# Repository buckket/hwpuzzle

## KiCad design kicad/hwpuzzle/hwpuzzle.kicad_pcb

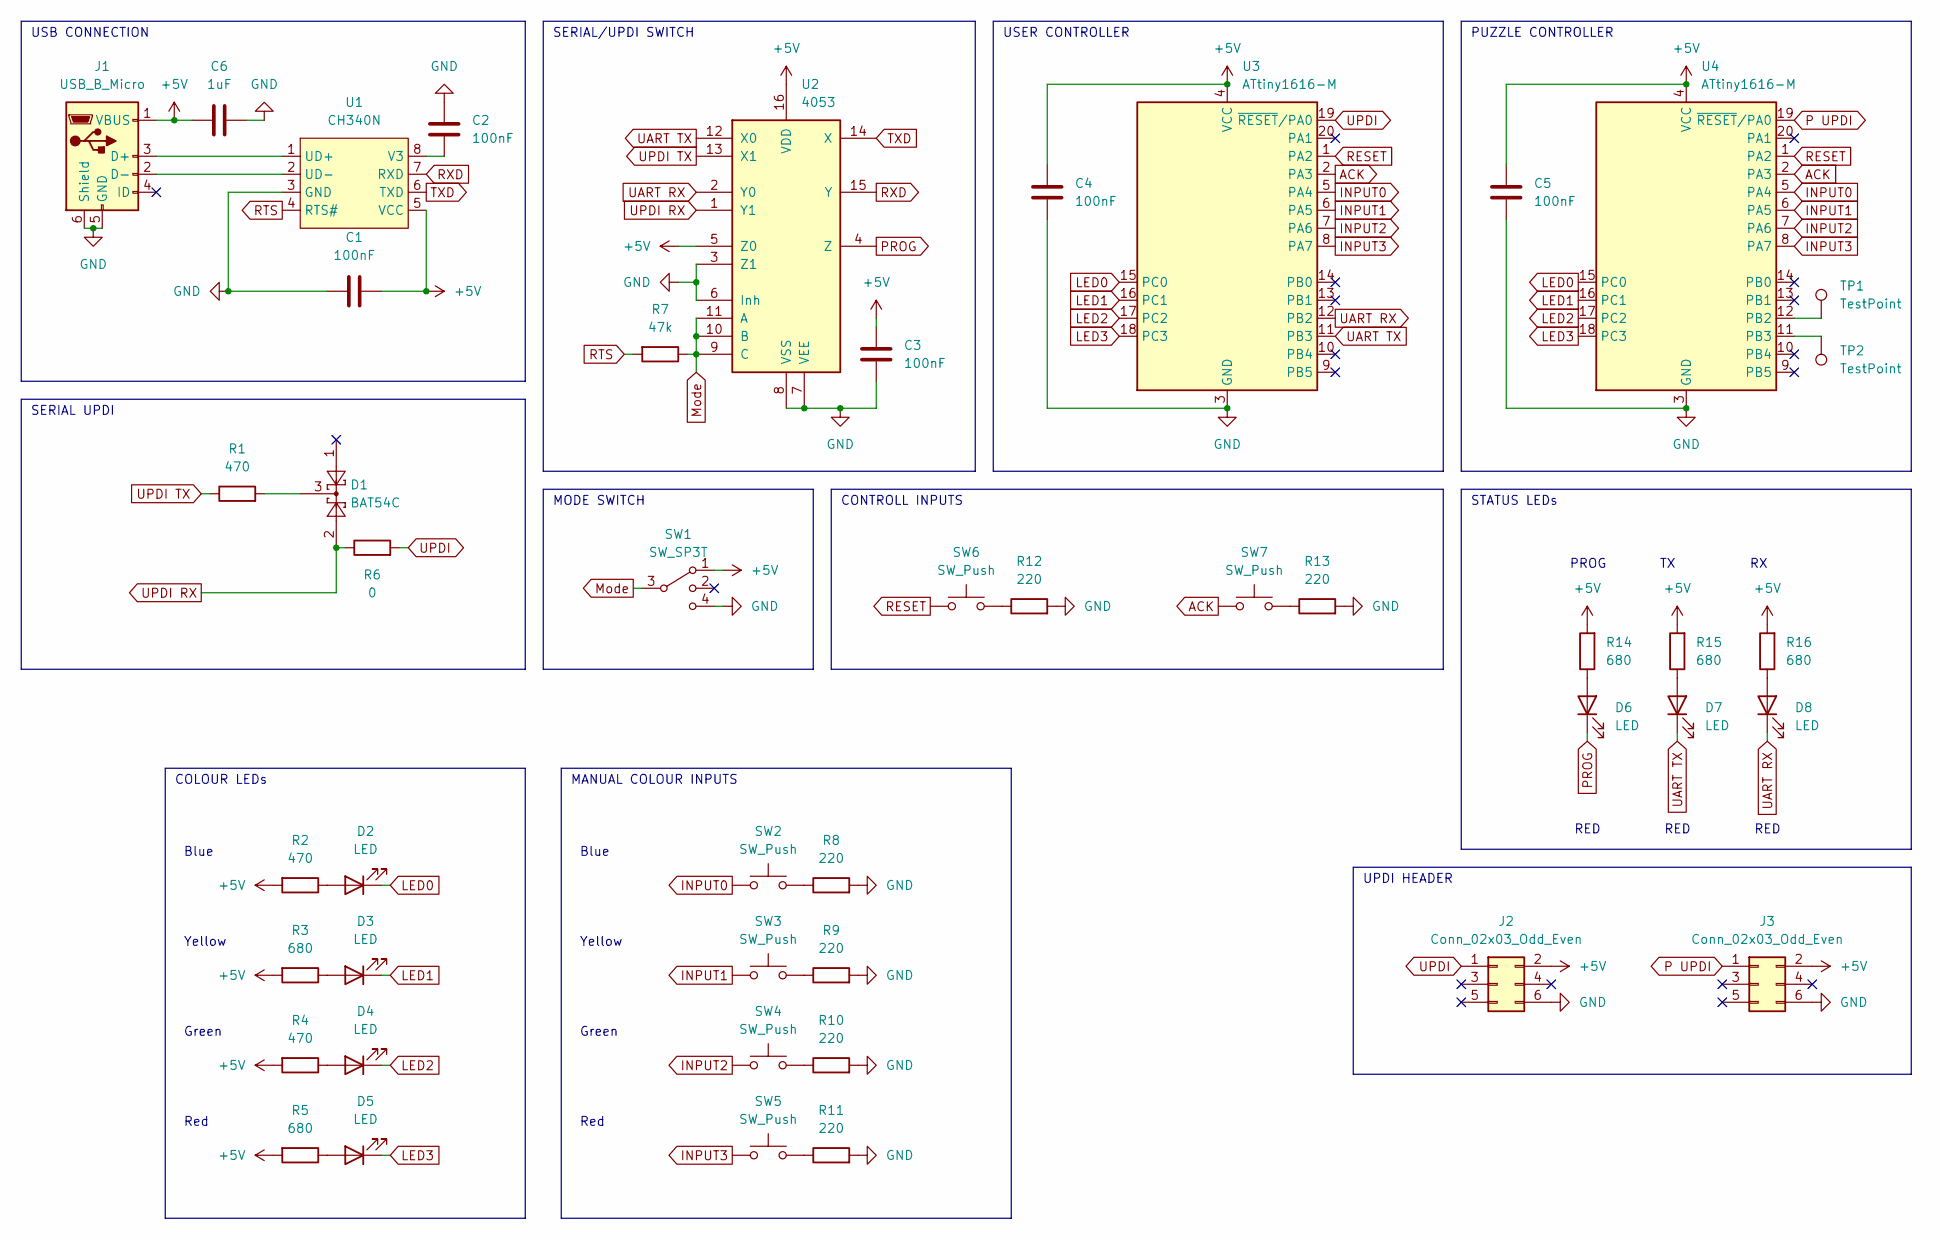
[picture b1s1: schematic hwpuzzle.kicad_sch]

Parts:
C1, C2, C3, C4, C5: 100nF; C_0402_1005Metric; MPN CL05B104KO5NNNC; LCSC C1525
C6: 1uF; C_0402_1005Metric; MPN CL05A105KA5NQNC; LCSC C52923
D1: BAT54C; SOT-23; MPN BAT54C,215; LCSC C37704
D2: LED; LED_0603_1608Metric; MPN 19-217/BHC-ZL1M2RY/3T; LCSC C72041
D3: LED; LED_0603_1608Metric; MPN 19-217/Y5C-AP1Q2/3T; LCSC C74343
D4: LED; LED_0603_1608Metric; MPN 19-217/GHC-YR1S2/3T; LCSC C72043
D5, D6, D7, D8: LED; LED_0603_1608Metric; MPN 19-217/R6C-AL1M2VY/3T; LCSC C72044
J1: USB_B_Micro; MicroXNJ; MPN MicroXNJ; LCSC C404969
J2, J3: Conn_02x03_Odd_Even; PinHeader_2x03_P2.54mm_Vertical; MPN DNP; LCSC DNP
R1, R2, R4: 470; R_0402_1005Metric; MPN 0402WGF4700TCE; LCSC C25117
R3, R5, R14, R15, R16: 680; R_0402_1005Metric; MPN 0402WGF6800TCE; LCSC C25130
R6: 0; R_0402_1005Metric; MPN 0402WGF0000TCE; LCSC C17168
R7: 47k; R_0402_1005Metric; MPN 0402WGF4702TCE; LCSC C25792
R8, R9, R10, R11, R12, R13: 220; R_0402_1005Metric; MPN 0402WGF2200TCE; LCSC C25091
SW1: SW_SP3T; SW_SP3T_PCM13; MPN SSSS812201; LCSC C160878
SW2, SW3, SW4, SW5, SW6, SW7: SW_Push; SW_SPST_TL3342; MPN TS-1187A-B-A-B; LCSC C318884
TP1, TP2: TestPoint; TestPoint_Pad_D1.0mm; MPN DNP; LCSC DNP
U1: CH340N; SOP-8_3.9x4.9mm_P1.27mm; MPN CH340N; LCSC C2977777
U2: 4053; TSSOP-16_4.4x5mm_P0.65mm; MPN CD4053BPWR; LCSC C106760
U3, U4: ATtiny1616-M; VQFN-20-1EP_3x3mm_P0.4mm_EP1.7x1.7mm; MPN ATTINY1616-MNR; LCSC C507118

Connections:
+5V: C1.2, C3.1, C4.1, C5.1, C6.1, J1.1 (VBUS), J2.2, J3.2, R2.2, R3.2, R4.2, R5.2, R14.2, R15.2, R16.2, SW1.1, U1.5 (VCC), U2.5 (Z0), U2.16 (VDD), U3.4 (VCC), U4.4 (VCC)
ACK: SW7.1, U3.2 (PA3), U4.2 (PA3)
GND: C1.1, C2.1, C3.2, C4.2, C5.2, C6.2, J1.5 (GND), J1.6 (Shield), J2.6, J3.6, R8.2, R9.2, R10.2, R11.2, R12.2, R13.2, SW1.4, U1.3 (GND), U2.3 (Z1), U2.6 (Inh), U2.7 (VEE), U2.8 (VSS), U3.3 (GND), U3.21 (GND), U4.3 (GND), U4.21 (GND)
INPUT0: SW2.1, U3.5 (PA4), U4.5 (PA4)
INPUT1: SW3.1, U3.6 (PA5), U4.6 (PA5)
INPUT2: SW4.1, U3.7 (PA6), U4.7 (PA6)
INPUT3: SW5.1, U3.8 (PA7), U4.8 (PA7)
LED0: D2.1 (K), U3.15 (PC0), U4.15 (PC0)
LED1: D3.1 (K), U3.16 (PC1), U4.16 (PC1)
LED2: D4.1 (K), U3.17 (PC2), U4.17 (PC2)
LED3: D5.1 (K), U3.18 (PC3), U4.18 (PC3)
Mode: R7.1, SW1.3, U2.9 (C), U2.10 (B), U2.11 (A)
unnamed: C2.2, U1.8 (V3)
unnamed: D1.3, R1.2
unnamed: D2.2 (A), R2.1
unnamed: D3.2 (A), R3.1
unnamed: D4.2 (A), R4.1
unnamed: D5.2 (A), R5.1
unnamed: D6.2 (A), R14.1
unnamed: D7.2 (A), R15.1
unnamed: D8.2 (A), R16.1
unnamed: J1.2 (D-), U1.2 (UD-)
unnamed: J1.3 (D+), U1.1 (UD+)
unnamed: R8.1, SW2.2
unnamed: R9.1, SW3.2
unnamed: R10.1, SW4.2
unnamed: R11.1, SW5.2
unnamed: R12.1, SW6.2
unnamed: R13.1, SW7.2
unnamed: TP1.1, U4.12 (PB2)
unnamed: TP2.1, U4.11 (PB3)
P UPDI: J3.1, U4.19 (~RESET/PA0)
PROG: D6.1 (K), U2.4 (Z)
RESET: SW6.1, U3.1 (PA2), U4.1 (PA2)
RTS: R7.2, U1.4 (RTS#)
RXD: U1.7 (RXD), U2.15 (Y)
TXD: U1.6 (TXD), U2.14 (X)
UART RX: D8.1 (K), U2.2 (Y0), U3.12 (PB2)
UART TX: D7.1 (K), U2.12 (X0), U3.11 (PB3)
UPDI: J2.1, R6.2, U3.19 (~RESET/PA0)
UPDI RX: D1.2, R6.1, U2.1 (Y1)
UPDI TX: R1.1, U2.13 (X1)

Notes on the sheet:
Blue
MANUAL COLOUR INPUTS
Red
PUZZLE CONTROLLER
Green
Yellow
RED
SERIAL UPDI
UPDI HEADER
PROG
CONTROLL INPUTS
SERIAL/UPDI SWITCH
USB CONNECTION
USER CONTROLLER
MODE SWITCH
STATUS LEDs
COLOUR LEDs

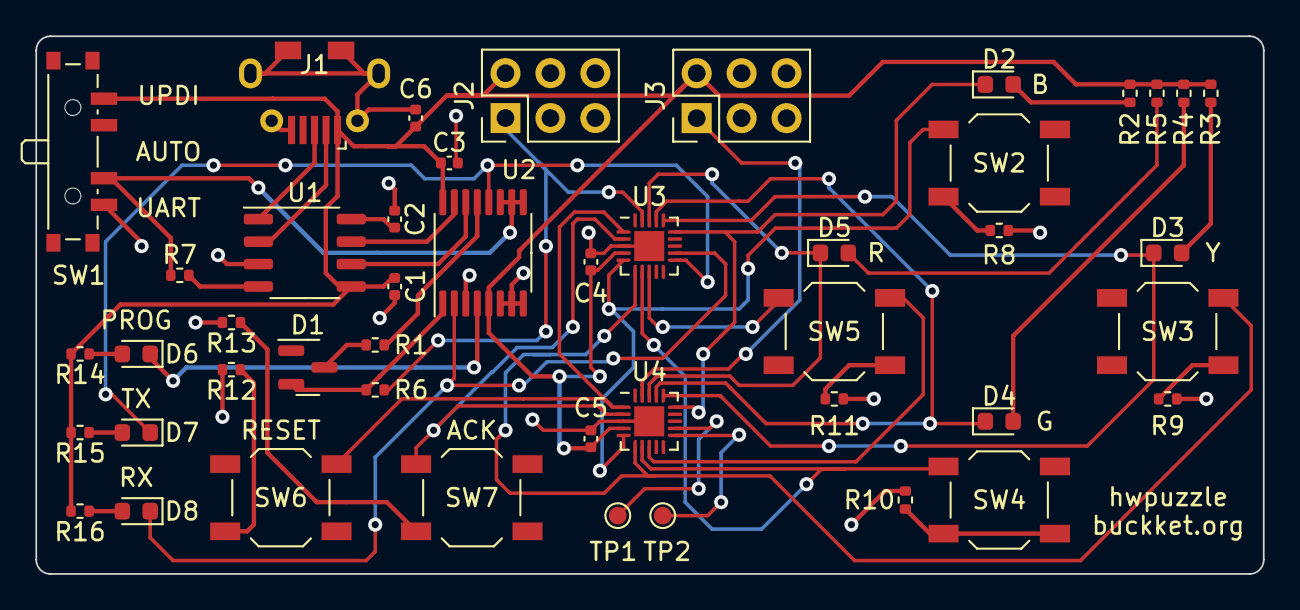
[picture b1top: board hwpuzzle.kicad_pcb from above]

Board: 2 copper layers, 69.4 x 30.4 mm, 46 parts (0 on the bottom side), 42 nets.

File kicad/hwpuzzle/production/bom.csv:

Designator,Footprint,Quantity,Value,LCSC Part #
"C1, C2, C3, C4, C5",C_0402_1005Metric,5,100nF,C1525
C6,C_0402_1005Metric,1,1uF,C52923
D1,SOT-23,1,BAT54C,C37704
"D2, D3, D4, D5, D6, D7, D8",LED_0603_1608Metric,7,LED,C72041
J1,MicroXNJ,1,USB_B_Micro,C404969
"J2, J3",PinHeader_2x03_P2.54mm_Vertical,2,Conn_02x03_Odd_Even,DNP
"R1, R2, R4",R_0402_1005Metric,3,470,C25117
"R10, R11, R12, R13, R8, R9",R_0402_1005Metric,6,220,C25091
"R14, R15, R16, R3, R5",R_0402_1005Metric,5,680,C25130
R6,R_0402_1005Metric,1,0,C17168
R7,R_0402_1005Metric,1,47k,C25792
SW1,SW_SP3T_PCM13,1,SW_SP3T,C160878
"SW2, SW3, SW4, SW5, SW6, SW7",SW_SPST_TL3342,6,SW_Push,C318884
"TP1, TP2",TestPoint_Pad_D1.0mm,2,TestPoint,DNP
U1,SOP-8_3.9x4.9mm_P1.27mm,1,CH340N,C2977777
U2,TSSOP-16_4.4x5mm_P0.65mm,1,4053,C106760
"U3, U4",VQFN-20-1EP_3x3mm_P0.4mm_EP1.7x1.7mm,2,ATtiny1616-M,C507118

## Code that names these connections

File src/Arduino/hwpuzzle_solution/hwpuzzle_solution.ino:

#include <HardwareSerial.h>

#define ENABLE_OUTPUTS
#define DELAY 18

#define STATE_READ 0
#define STATE_WRITE 1
#define STATE_FINISHED 2

int STATE = 0;
int BUFFER[100] = {0};
int TO_READ = 1;
int TO_WRITE = 0;

void setup() {
  // Set Reset as INPUT
  pinMode(PIN_PA2, INPUT);

  // Set LED0-4 as INPUT
  pinMode(PIN_PC0, INPUT);
  pinMode(PIN_PC1, INPUT);
  pinMode(PIN_PC2, INPUT);
  pinMode(PIN_PC3, INPUT);

#ifdef ENABLE_OUTPUTS
  //Set INPUT0-4 as OUTPUT
  pinMode(PIN_PA3, OUTPUT);
  pinMode(PIN_PA4, OUTPUT);
  pinMode(PIN_PA5, OUTPUT);
  pinMode(PIN_PA6, OUTPUT);
  pinMode(PIN_PA7, OUTPUT);
#endif

  // Write HIGH (active-low)
  digitalWrite(PIN_PA3, HIGH);
  digitalWrite(PIN_PA4, HIGH);
  digitalWrite(PIN_PA5, HIGH);
  digitalWrite(PIN_PA6, HIGH);
  digitalWrite(PIN_PA7, HIGH);

  // Init Serial
  Serial.begin(115200);
  while (!Serial) {
    ; // wait for serial port to connect. Needed for native USB port only
  }

  Serial.write("Up and running!\n");
}

void toggle_pin(int pin) {
  digitalWrite(pin, LOW);
  delay(DELAY);
  digitalWrite(pin, HIGH);
  delay(DELAY);
}

void decode_message() {
  Serial.printf("Message length: %d\n", TO_WRITE);

  for (int i = 0; i < TO_WRITE / 4; i++) {
    int x = 0;
    x += 1 * BUFFER[i * 4 + 0];
    x += 4 * BUFFER[i * 4 + 1];
    x += 16 * BUFFER[i * 4 + 2];
    x += 64 * BUFFER[i * 4 + 3];
    Serial.print((char)x);
  }
}

int read_pins() {
  int led_0 = !digitalRead(PIN_PC0);
  int led_1 = !digitalRead(PIN_PC1);
  int led_2 = !digitalRead(PIN_PC2);
  int led_3 = !digitalRead(PIN_PC3);

  int sum = led_0 + led_1 + led_2 + led_3;
  if (sum == 2) {
    return 4;
  } else if (sum == 4) {
    return 5;
  }


  if (led_0 > 0) return 0;
  if (led_1 > 0) return 1;
  if (led_2 > 0) return 2;
  if (led_3 > 0) return 3;

  return -1;
}

void loop() {
  if (digitalRead(PIN_PA2) == LOW)  {
    TO_READ = 1;
    TO_WRITE = 0;
    STATE = STATE_READ;
    toggle_pin(PIN_PA3);
    Serial.print("RESET detected\n");
    delay(500);
  }
  switch (STATE) {
    case STATE_READ:
      toggle_pin(PIN_PA3);
      for (int i = 0; i < TO_READ; i++) {
        int input = read_pins();
        if (input >= 0 && input < 4) {
          BUFFER[i] = input;
          Serial.printf("Detected %d\n", input);
          toggle_pin(PIN_PA3);
          continue;
        }
        if (input == 4) {
          STATE = STATE_FINISHED;
          Serial.print("We are finished, decoding input\n");
          decode_message();
          break;
        }
        if (input == 5) {
          Serial.print("There has been an error, retrying\n");
          TO_READ = 1;
          TO_WRITE = 0;
          toggle_pin(PIN_PA3);
          break;
        }
        if (input == -1) {
          Serial.print("NO LED active, try writing\n");
          TO_READ++;
          TO_WRITE++;
          STATE = STATE_WRITE;
          toggle_pin(PIN_PA3);
          break;
        }
      }
      break;
    case STATE_WRITE:
      for (int i = 0; i < TO_WRITE; i++) {
        Serial.printf("Writing %d\n", BUFFER[i]);
        if (BUFFER[i] == 0) toggle_pin(PIN_PA4);
        if (BUFFER[i] == 1) toggle_pin(PIN_PA5);
        if (BUFFER[i] == 2) toggle_pin(PIN_PA6);
        if (BUFFER[i] == 3) toggle_pin(PIN_PA7);
      }
      STATE = STATE_READ;
      break;
    case STATE_FINISHED:
      toggle_pin(PIN_PA3);
      delay(100);
      break;
  }
}

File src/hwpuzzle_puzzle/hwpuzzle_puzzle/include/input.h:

#ifndef INPUT_H_
#define INPUT_H_

#include <avr/io.h>
#include <avr/interrupt.h>

// PORTA
#define RESET_PIN		PIN2_bm
#define ACK_PIN			PIN3_bm
#define INPUT0_PIN		PIN4_bm
#define INPUT1_PIN		PIN5_bm
#define INPUT2_PIN		PIN6_bm
#define INPUT3_PIN		PIN7_bm

void input_init(void);
uint8_t input_get_key_press(uint8_t key_mask);
uint8_t input_get_key_state(uint8_t key_mask);

#endif /* INPUT_H_ */

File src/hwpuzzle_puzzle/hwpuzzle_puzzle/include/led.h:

#ifndef LED_H_
#define LED_H_

#include <avr/io.h>

// PORTC
#define LED0_PIN		PIN0_bm
#define LED1_PIN		PIN1_bm
#define LED2_PIN		PIN2_bm
#define LED3_PIN		PIN3_bm

void LED_init(void);
void LED_set(uint8_t out);

#endif /* LED_H_ */

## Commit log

2023-02-17 Update PCB, add docs
2023-04-05 Update docs
2023-04-05 Update PCB
2023-04-05 Add Arduino solution
2023-04-05 Add puzzle controller code
2023-04-05 Add website code
2025-03-21 Bump github.com/golang-jwt/jwt/v5 from 5.0.0-rc.1 to 5.2.2 in /puzzle
    Bumps [github.com/golang-jwt/jwt/v5](https://github.com/golang-jwt/jwt) from 5.0.0-rc.1 to 5.2.2.
    - [Release notes](https://github.com/golang-jwt/jwt/releases)
    - [Changelog](https://github.com/golang-jwt/jwt/blob/main/VERSION_HISTORY.md)
    - [Commits](https://github.com/golang-jwt/jwt/compare/v5.0.0-rc.1...v5.2.2)
    ---
    updated-dependencies:
